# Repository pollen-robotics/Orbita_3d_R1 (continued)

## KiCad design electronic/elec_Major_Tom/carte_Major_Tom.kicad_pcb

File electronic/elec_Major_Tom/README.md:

# Major Tom Electronic Board

Major Tom is a power board driving 3 BLDC motors. It also add 3 temperature measurements and a fan control.

<div align="center"></div>

## Basically
 - 55 x 54 mm
 - Powered in 12V or in 24V.
 - Drive 3 BLDC motors with DRV8313 (2,5 A peak)
 - Designed with KiCAD 6.

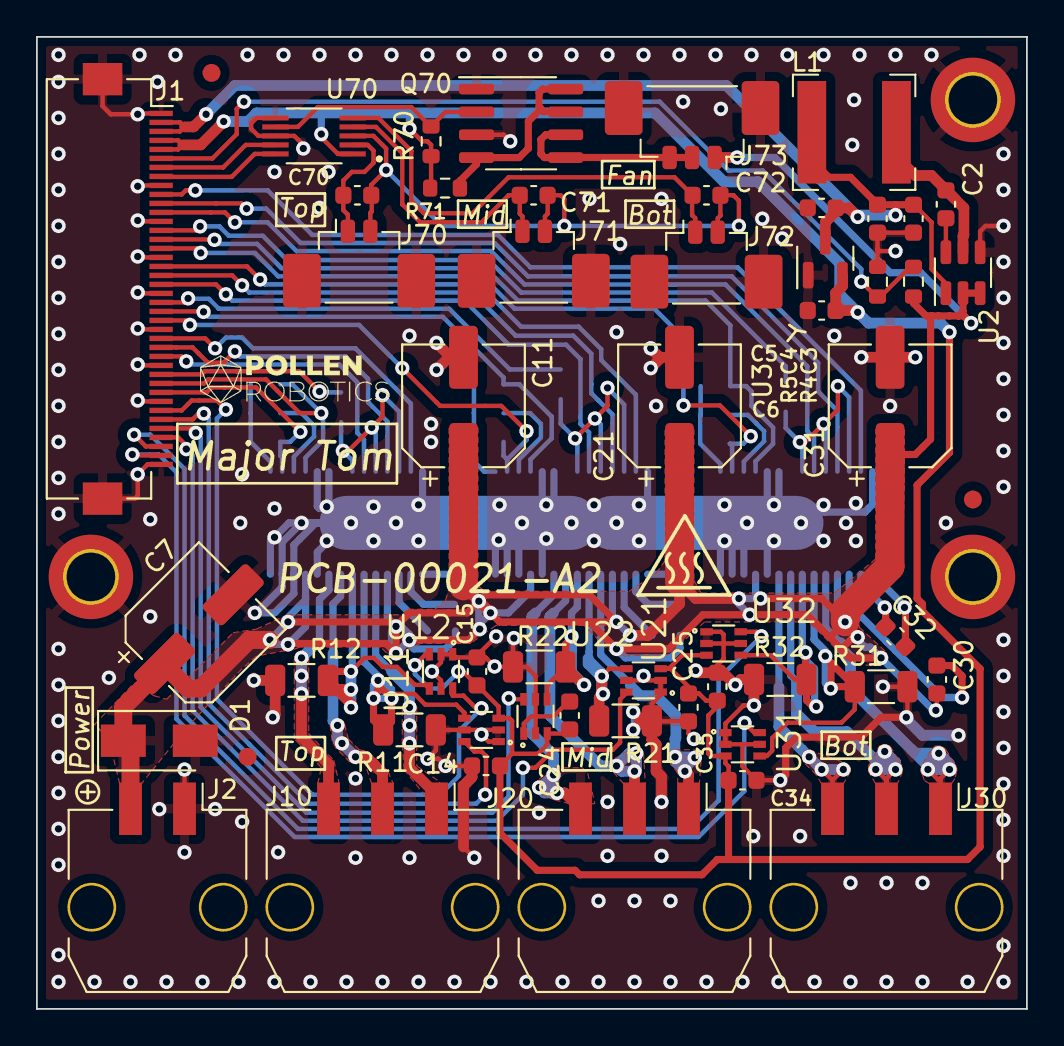
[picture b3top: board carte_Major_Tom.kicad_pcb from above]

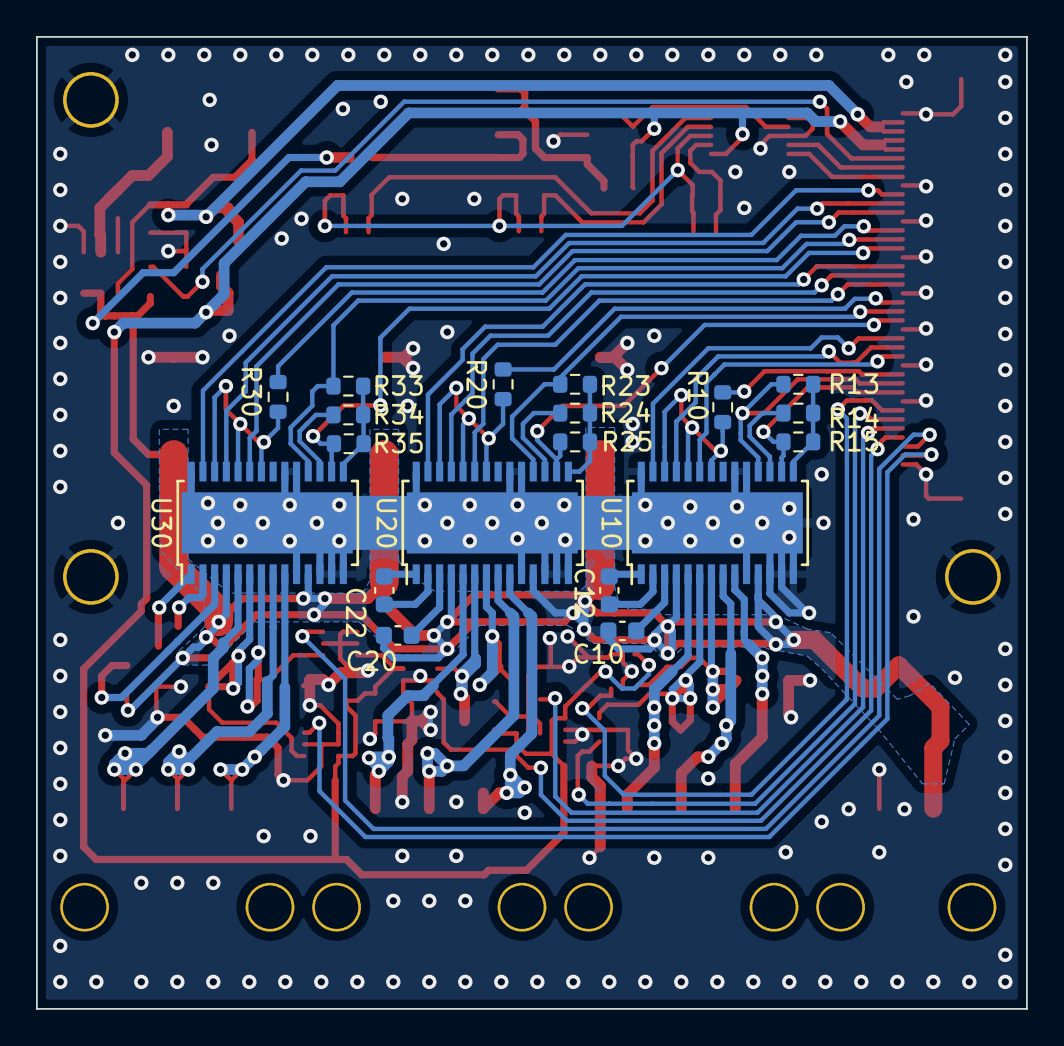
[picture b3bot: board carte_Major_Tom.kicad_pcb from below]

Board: 2 copper layers, 55.0 x 54.0 mm, 78 parts (19 on the bottom side), 73 nets.

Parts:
C2, C10, C14, C15, C20, C24, C25, C30, C34, C35: 100n 63V; C_0603_1608Metric
C3, C4: 22u 6V3; C_0603_1608Metric
C5, C6: 1u 6V3; C_0603_1608Metric
C7, C11, C21, C31: 10u 63V; CP_Elec_6.3x7.7
C12, C22, C32: 10n 63V; C_0603_1608Metric
C70, C71, C72: 100p; C_0603_1608Metric
D: D_TVS_uni; D_SMA
FID1, FID2, FID3: DNP Fiducial; Fiducial_1mm_Mask2mm
H1, H2, H3: DNP MountingHole_Pad; MountingHole_2.7mm_M2.5_DIN965_Pad_TopOnly
H6: DNP Logo Pollen 2021; Logo_Pollen_2021_sq
J1: FFC 0,5 mm 40w; Hirose_FH12-40S-0.5SH_1x40-1MP_P0.50mm_Horizontal
J2: MicroFit2; Molex_Micro-Fit_3.0_43650-0210_1x02-1MP_P3.00mm_Horizontal
J10, J20, J30: MicroFit3; Molex_Micro-Fit_3.0_43650-0310_1x03-1MP_P3.00mm_Horizontal
J70, J71, J72: Pico2; Molex_PicoBlade_53398-0271_1x02-1MP_P1.25mm_Vertical
J73: Pico3; Molex_PicoBlade_53398-0371_1x03-1MP_P1.25mm_Vertical
L1: 6,8u 2A; L_Bourns-SRN6028
Q70: AUIRF7341Q; SOIC-8_3.9x4.9mm_P1.27mm
R4: 180k; R_0603_1608Metric
R5: 20k; R_0603_1608Metric
R10, R13, R14, R15, R20, R23, R24, R25, R30, R33, R34, R35: 10k; R_0603_1608Metric
R11, R12, R21, R22, R31, R32: 10m; R_1206_3216Metric
R70, R71: 100k; R_0603_1608Metric
SYM1: SYM_Hot_Small; logo_hot
U2: AP63205; TSOT-23-6
U3: MCP1700T; SOT-23
U10, U20, U30: DRV8313; HTSSOP-28-1EP_4.4x9.7mm_P0.65mm_EP3.4x9.5mm
U11, U12, U21, U22, U31, U32: NCS214; SC70-6
U70: MAX31730; SOP50P490X110-10N

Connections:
+3V3: C6.2, C14.2, C15.2, C24.2, C25.2, C34.2, C35.2, J1.4, J1.5, R70.2, R71.2, U3.2 (VO), U11.3 (Vs), U12.3 (Vs), U21.3 (Vs), U22.3 (Vs), U31.3 (Vs), U32.3 (Vs), U70.1 (VDD)
+5V: C3.1, C4.1, C5.1, J1.2, J1.3, L1.1, U2.1 (FB), U3.3 (VI)
+BATT: C7.1, C10.1, C11.1, C20.1, C21.1, C30.1, C31.1, D.1 (A1), J2.2, J73.1, R4.2, U2.2 (EN), U2.3 (IN), U10.4 (VM), U10.11 (VM), U20.4 (VM), U20.11 (VM), U30.4 (VM), U30.11 (VM)
/Fan control/SCL: J1.8, U70.10 (SCL)
/Fan control/SDA: J1.7, U70.9 (SDA)
/Microcontroller/MBotCurrent_A: J1.39, U31.6 (OUT)
/Microcontroller/MBotCurrent_B: J1.38, U32.6 (OUT)
/Microcontroller/MBotPWM_A: J1.10, U30.27 (In1)
/Microcontroller/MBotPWM_B: J1.11, U30.25 (In2)
/Microcontroller/MBotPWM_C: J1.12, U30.23 (In3)
/Microcontroller/MBot_En: J1.14, R30.1
/Microcontroller/MBot_nFault: J1.15, R33.1, U30.18 (nFault)
/Microcontroller/MBot_nRST: J1.16, R35.2, U30.16 (nReset)
/Microcontroller/MMidCurrent_A: J1.37, U21.6 (OUT)
/Microcontroller/MMidCurrent_B: J1.36, U22.6 (OUT)
/Microcontroller/MMidPWM_A: J1.18, U20.27 (In1)
/Microcontroller/MMidPWM_B: J1.19, U20.25 (In2)
/Microcontroller/MMidPWM_C: J1.20, U20.23 (In3)
/Microcontroller/MMid_En: J1.22, R20.1
/Microcontroller/MMid_nFault: J1.23, R23.1, U20.18 (nFault)
/Microcontroller/MMid_nRST: J1.24, R25.2, U20.16 (nReset)
/Microcontroller/MTopCurrent_A: J1.35, U11.6 (OUT)
/Microcontroller/MTopCurrent_B: J1.34, U12.6 (OUT)
/Microcontroller/MTopPWM_A: J1.26, U10.27 (In1)
/Microcontroller/MTopPWM_B: J1.27, U10.25 (In2)
/Microcontroller/MTopPWM_C: J1.28, U10.23 (In3)
/Microcontroller/MTop_En: J1.30, R10.1
/Microcontroller/MTop_nFault: J1.31, R13.1, U10.18 (nFault)
/Microcontroller/MTop_nRST: J1.32, R15.2, U10.16 (nReset)
/Microcontroller/Vbatt_div_10: J1.6, R4.1, R5.2
/Motors/3V3_Drv1: R13.2, R14.1, R15.1, U10.15 (V3P3)
/Motors/3V3_Drv2: R23.2, R24.1, R25.1, U20.15 (V3P3)
/Motors/3V3_Drv3: R33.2, R34.1, R35.1, U30.15 (V3P3)
/Motors/MBotPh1: J30.1, U30.5 (Out1)
/Motors/MBotPh2: J30.2, U30.8 (Out2)
/Motors/MBotPh3: J30.3, U30.9 (Out3)
/Motors/MMidPh1: J20.1, U20.5 (Out1)
/Motors/MMidPh2: J20.2, U20.8 (Out2)
/Motors/MMidPh3: J20.3, U20.9 (Out3)
/Motors/MTopPh1: J10.1, U10.5 (Out1)
/Motors/MTopPh2: J10.2, U10.8 (Out2)
/Motors/MTopPh3: J10.3, U10.9 (Out3)
GND: C3.2, C4.2, C5.2, C6.1, C7.2, C11.2, C14.1, C15.1, C21.2, C24.1, C25.1, C31.2, C34.1, C35.1, D.2 (A2), H1.1, H2.1, H3.1, J1.1, J1.9, J1.13, J1.17, J1.21, J1.25, J1.29, J1.33, J1.40, J1.MP (MountPin), J2.1, J70.MP (MountPin), J71.MP (MountPin), J72.MP (MountPin), J73.MP (MountPin), Q70.1 (S1), Q70.3 (S2), R5.1, R11.2, R12.2, R21.2, R22.2, R31.2, R32.2, U2.4 (GND), U3.1 (GND), U10.10 (PGnd3), U10.12 (CompP), U10.13 (CompN), U10.14 (Gnd), U10.19 (nCompo), U10.20 (Gnd), U10.28 (Gnd), U10.29 (Thermal_Pad), U11.1 (REF), U11.2 (GND), U11.5 (-IN), U12.1 (REF), U12.2 (GND), U12.5 (-IN), U20.10 (PGnd3), U20.12 (CompP), U20.13 (CompN), U20.14 (Gnd), U20.19 (nCompo), U20.20 (Gnd), U20.28 (Gnd), U20.29 (Thermal_Pad), U21.1 (REF), U21.2 (GND), U21.5 (-IN), U22.1 (REF), U22.2 (GND), U22.5 (-IN), U30.10 (PGnd3), U30.12 (CompP), U30.13 (CompN), U30.14 (Gnd), U30.19 (nCompo), U30.20 (Gnd), U30.28 (Gnd), U30.29 (Thermal_Pad), U31.1 (REF), U31.2 (GND), U31.5 (-IN), U32.1 (REF), U32.2 (GND), U32.5 (-IN), U70.6 (GND), U70.8 (ADD)
unnamed: C2.1, U2.6 (BST)
unnamed: C2.2, L1.2, U2.5 (SW)
unnamed: C10.2, U10.3 (VCP)
unnamed: C12.1, U10.1 (CPL)
unnamed: C12.2, U10.2 (CPH)
unnamed: C20.2, U20.3 (VCP)
unnamed: C22.1, U20.1 (CPL)
unnamed: C22.2, U20.2 (CPH)
unnamed: C30.2, U30.3 (VCP)
unnamed: C32.1, U30.1 (CPL)
unnamed: C32.2, U30.2 (CPH)
unnamed: C70.1, C71.1, C72.1, J70.2, J71.2, J72.2, U70.3 (DXN)
unnamed: C70.2, J70.1, U70.2 (DXP1)
unnamed: C71.2, J71.1, U70.4 (DXP2)
unnamed: C72.2, J72.1, U70.5 (DXP3)
unnamed: J73.2, J73.3, Q70.5 (D2), Q70.6 (D2)
unnamed: Q70.2 (G1), R70.1, U70.7 (~THERM)
unnamed: Q70.4 (G2), Q70.7 (D1), Q70.8 (D1), R71.1
unnamed: R10.2, U10.22 (En3), U10.24 (En2), U10.26 (En1)
unnamed: R11.1, U10.6 (PGnd1), U11.4 (+IN)
unnamed: R12.1, U10.7 (PGnd2), U12.4 (+IN)
unnamed: R14.2, U10.17 (nSleep)
unnamed: R20.2, U20.22 (En3), U20.24 (En2), U20.26 (En1)
unnamed: R21.1, U20.6 (PGnd1), U21.4 (+IN)
unnamed: R22.1, U20.7 (PGnd2), U22.4 (+IN)
unnamed: R24.2, U20.17 (nSleep)
unnamed: R30.2, U30.22 (En3), U30.24 (En2), U30.26 (En1)
unnamed: R31.1, U30.6 (PGnd1), U31.4 (+IN)
unnamed: R32.1, U30.7 (PGnd2), U32.4 (+IN)
unnamed: R34.2, U30.17 (nSleep)

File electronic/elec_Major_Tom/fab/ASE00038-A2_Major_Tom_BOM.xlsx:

ASE00038 | A2 | Major Tom | 44935
Ref. | Value | Description | Qtty | Man. | Man. Ref.
C2, C10, C14, C15, C20, C24, C25, C30, C34, C35 | 100n 63V | Capa 0603 | 10 | TDK | CGA3E2X7R1H104K080AA
C3, C4 | 22u 6V3 | Capa 0603 | 2 | Murata | GRM188R61A226ME15D
C5, C6 | 1u 6V3 | Capa 0603 | 2 | TDK | C1608X7R1A105K080AC
C7, C11, C21, C31 | 10u 63V | Capa diam. 6,3 / pas 7,7 | 4 | Multicomp | MCESL100V106M6.3X7.7
C12, C22, C32 | 10n 63V | Capa 0603 | 3 | TDK | CGA3E2C0G1H103J080AA
C70, C71, C72 | DNP-100p | Capa 0603 | 3
D1 | DNP-D_TVS_uni | Diode TVS unidir. 12V | 1 | STMicro | SMAJ12A
J1 | FFC 0,5 mm 40w | Microcontroller Connector | 1 | Hirose | FH12-40S-0.5SH(55)
J2 | MicroFit2 | Power Supply Connector | 1 | Molex | 43650-0210
J10, J20, J30 | MicroFit3 | Motor Phases Connector | 3 | Molex | 43650-0310
J70, J71, J72 | DNP-Pico2 | Temperature Connector | 3 | Molex | 53398-0271
J73 | DNP-Pico3 | Fan Connector | 1 | Molex | 53398-0371
L1 | 6,8u 2A | Inductor 6,8u 2A 6x6 mm | 1 | Bourns | SRN6045TA-6R8M
Q70 | DNP-AUIRF7341Q | DNP-MOSFET Double | 1 | Infineon | AUIRF7341Q
R4 | 180k | Res. 0603 | 1 | Yageo | RC0603FR-07180KL
R5 | 20k | Res. 0603 | 1 | Yageo | RC0603FR-0720KL
R10, R13, R14, R15, R20, R23, R24, R25, R30, R33, R34, R35 | 10k | Res. 0603 | 12 | Yageo | RC0603FR-0710KL
R11, R12, R21, R22, R31, R32 | 10m | Power Res. 10m 1206 0,2W | 6 | Panasonic | ERJ8CWFR010V
R70, R71 | DNP-100k | DNP-Res. 0603 | 2
U2 | AP63205 | DC-DC buck converter -> 5V | 1 | Diodes Inc. | AP63205WU
U3 | MCP1700T | LDO Regulator -> 3V3 | 1 | MicroChip | MCP1700T-3302E/TT
U10, U20, U30 | DRV8313 | BLDC Driver 2,5A peak | 3 | TI | DRV8313PWP
U11, U12, U21, U22, U31, U32 | NCS214 | Current Sense Amplifier x100 | 6 | ON Semi | NCS214RSQT2G
U70 | DNP-MAX31730 | DNP-Temperature + Fan Controller | 1 | Maxim Integrated | MAX31730AUB+

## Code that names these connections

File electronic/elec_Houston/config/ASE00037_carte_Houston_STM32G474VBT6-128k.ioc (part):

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Mcu.Name=STM32G474V(B-C-E)Tx
Mcu.Package=LQFP100
Mcu.UserName=STM32G474VBTx
PA0.Mode=IN1-Single-Ended
PA0.Signal=ADC1_IN1
PA1.Mode=IN2-Single-Ended
PA1.Signal=ADC1_IN2
PA10.Signal=S_TIM1_CH3
PA11.Mode=Device
PA11.Signal=USB_DM
PA12.Mode=Device
PA12.Signal=USB_DP
PA13.Mode=Serial_Wire
PA13.Signal=SYS_JTMS-SWDIO
PA14.Mode=Serial_Wire
PA14.Signal=SYS_JTCK-SWCLK
PA15.Signal=S_TIM2_CH1
PA3.Signal=GPIO_Output
PA4.Signal=GPIO_Output
PA5.Mode=Full_Duplex_Master
PA5.Signal=SPI1_SCK
PA6.Mode=IN3-Single-Ended
PA6.Signal=ADC2_IN3
PA7.Mode=IN4-Single-Ended
PA7.Signal=ADC2_IN4
PA8.Signal=S_TIM1_CH1
PA9.Signal=S_TIM1_CH2
PB1.Mode=IN1-Single-Ended
PB1.Signal=ADC3_IN1
PB10.Mode=Asynchronous
PB10.Signal=USART3_TX
PB11.Mode=Asynchronous
PB11.Signal=USART3_RX
PB12.Signal=GPIO_Output
PB13.Signal=GPIO_Output
PB14.Signal=GPIO_Output
PB2.Signal=S_TIM5_CH1
PB3.Signal=SYS_JTDO-SWO
PB4.Mode=Full_Duplex_Master
PB4.Signal=SPI1_MISO
PB5.Mode=Full_Duplex_Master
PB5.Signal=SPI1_MOSI
PB6.Signal=GPIO_Output
PB7.Signal=GPIO_Output
PC1.Signal=GPIO_Output
PC12.Signal=S_TIM5_CH2
PC13.Signal=GPIO_Output
PC2.Signal=GPIO_Output
PC3.Signal=GPIO_Input
PC4.Mode=I2C
PC4.Signal=I2C2_SCL
PC6.Signal=S_TIM8_CH1
PC7.Signal=S_TIM8_CH2
PC8.Signal=S_TIM8_CH3
PD10.Signal=GPIO_Output
PD11.Signal=GPIO_Input
PD12.Signal=S_TIM4_CH1
PD13.Signal=S_TIM4_CH2
PD14.Signal=S_TIM4_CH3
PD2.Signal=S_TIM3_ETR
PD3.Signal=S_TIM2_ETR
PD4.Signal=S_TIM2_CH2
PD7.Signal=S_TIM2_CH3
PD9.Signal=GPIO_Output
PE0.Signal=GPIO_Output
PE10.Signal=GPIO_Output
PE11.Signal=GPIO_Output
PE12.Signal=GPIO_Input
PE14.Mode=IN1-Single-Ended
PE14.Signal=ADC4_IN1
PE15.Mode=IN2-Single-Ended
PE15.Signal=ADC4_IN2
PE2.Signal=S_TIM3_CH1
PE3.Signal=S_TIM3_CH2
PE4.Signal=S_TIM3_CH3
PE7.Signal=S_TIM1_ETR
PE8.Signal=S_TIM5_CH3
PE9.Mode=IN2-Single-Ended
PE9.Signal=ADC3_IN2
PF0-OSC_IN.Mode=I2C
PF0-OSC_IN.Signal=I2C2_SDA
RCC.HSE_VALUE=8000000
RCC.SYSCLKFreq_VALUE=168000000
RCC.SYSCLKSource=RCC_SYSCLKSOURCE_PLLCLK
board=custom

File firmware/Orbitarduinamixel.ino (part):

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uint8_t orbita_firmware_rev = ORBITARDUINAMIXEL_REV;


#define GREEN_LED  PE0
#define RED_LED    PC13
#define TEST_PIN_2 PB12 // Now used as Bot_Motor_Phase_B
#define TEST_PIN_3 PB13 // Now used as Bot_Motor_Phase_C
#define TEST_PIN_4 PA7

#define WATCHDOG_DELAY 4000000 // us

//      Top

const byte topCSA     = PA0;
const byte topCSB     = PA1;
const byte topEncA    = PA8;
const byte topEncB    = PA9;
const byte topEncI    = PE7;
const byte topHallA   = PA8;
const byte topHallB   = PA9;
const byte topHallC   = PA10;
const byte topMotA    = PD12;
const byte topMotB    = PD13;
const byte topMotC    = PD14;
const byte topMotEn   = PD9;
const byte topMotnRST = PD10;
const byte topMotnFlt = PD11;
#define TOP_MOTOR_CMD 'T'

//      Middle
const byte midCSA     = PB1;
const byte midCSB     = PE9;
const byte midEncA    = PA15;
const byte midEncB    = PD4;
const byte midEncI    = PD3;
const byte midHallA   = PA15;
const byte midHallB   = PD4;
const byte midHallC   = PD7;
const byte midMotA    = PB2;
const byte midMotB    = PC12;
const byte midMotC    = PE8;
const byte midMotEn   = PC1;
const byte midMotnRST = PC2;
const byte midMotnFlt = PC3;
#define MID_MOTOR_CMD 'M'

//      Bottom
const byte botCSA     = PE14;
const byte botCSB     = PE15;
const byte botEncA    = PE2;
const byte botEncB    = PE3;
const byte botEncI    = PD2;
const byte botHallA   = PE2;
const byte botHallB   = PE6; // PE3 on Houston-A1 base
const byte botHallC   = PC0; // PE4 on Houston-A1 base
const byte botMotA    = PC6;
const byte botMotB    = PC7;
const byte botMotC    = PC8;
const byte botMotEn   = PE10;
const byte botMotnRST = PE11;
const byte botMotnFlt = PE12;
#define BOT_MOTOR_CMD 'B'


//      Orbita Magnetic Sensor
const byte orbitaSPI_MOSI  = PB5;
const byte orbitaSPI_MISO  = PB4;
const byte orbitaSPI_SCK   = PA5;
const byte orbitaTopSPI_CS = PA4;
const byte orbitaMidSPI_CS = PB7;
const byte orbitaBotSPI_CS = PB6;
#define ORBITA_SENSOR_TYPE AS5047_SPI

//      Orbita IMU
const byte orbitaIMU_Acc_CS = PA3;
const byte orbitaIMU_Gyr_CS = PB9;

/************************ Motors ***********************/
// Maxon ECX Torque 22 M
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
/*******************************************************/

HardwareSerial Serial3(PB11, PB10);  // Houston-J7

void top_init();
void mid_init();
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
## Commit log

2024-11-13 [added] Cables/Firmware/Electronic
2024-11-13 [added] Production files for Electronic
2024-11-13 [added] Licences + pictures.
2024-11-13 [fixed] image selection
2024-11-13 [added] Mechanical parts
2024-11-13 [added] Full Orbita_3d model
2024-11-13 [added] Screeshot of Full assembly
